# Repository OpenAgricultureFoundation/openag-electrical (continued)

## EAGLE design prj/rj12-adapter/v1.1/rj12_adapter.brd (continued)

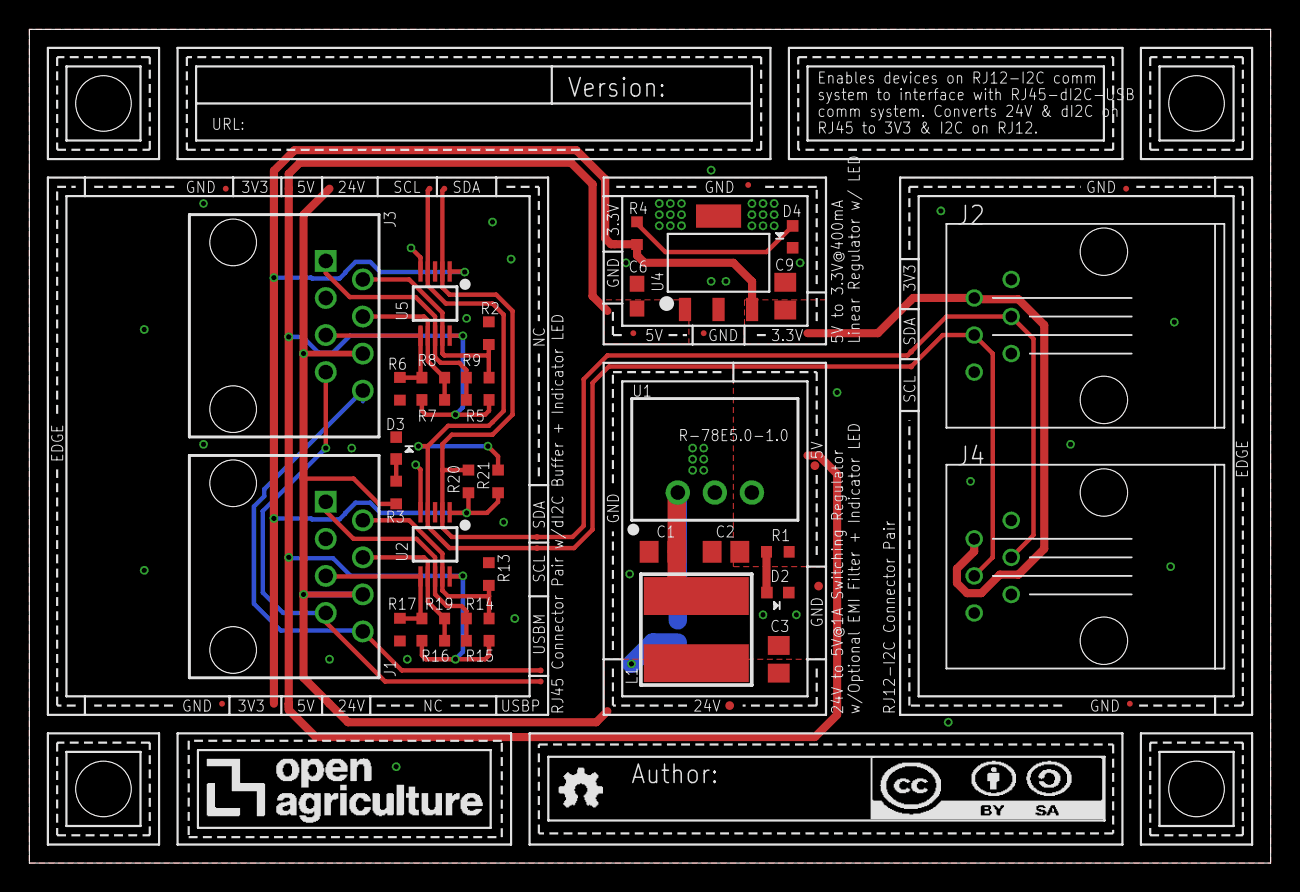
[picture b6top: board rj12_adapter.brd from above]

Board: 2 copper layers, 85.1 x 57.1 mm, 70 parts (1 on the bottom side), 20 nets.

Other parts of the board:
U$1, U$2, U$3, U$4: CORNER
U$5: LOGO
U$9: CAMBRIDGE-MAP-RJ12-ADAPTER-V-1-1
